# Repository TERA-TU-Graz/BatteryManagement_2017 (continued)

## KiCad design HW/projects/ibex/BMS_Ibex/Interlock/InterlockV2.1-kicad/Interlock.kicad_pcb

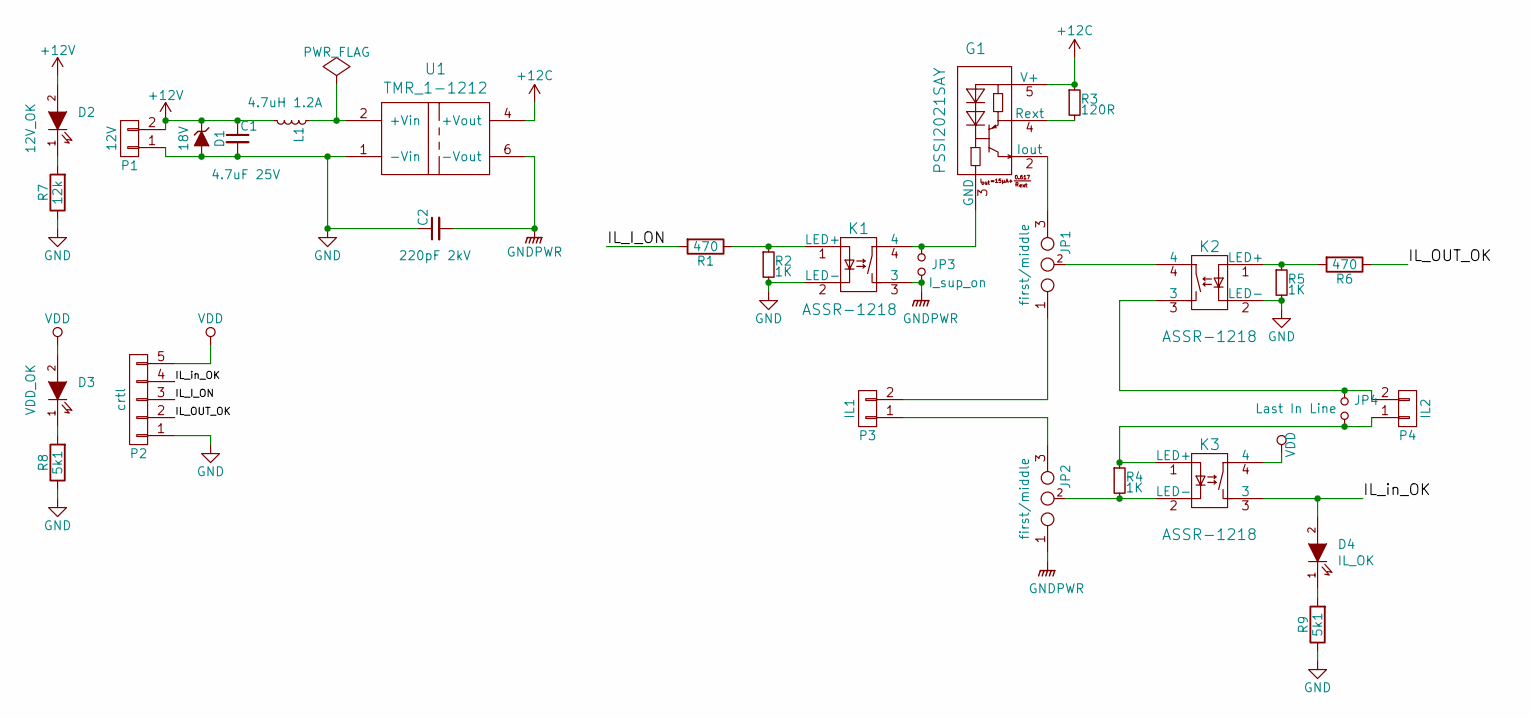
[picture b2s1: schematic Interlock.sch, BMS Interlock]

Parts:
C1: 4.7uF 25V; C_0805in
C2: 220pF 2kV; C_1206in_HV
D1: 18V; DO-214AA
D2: 12V_OK; LED_0805
D3: VDD_OK; LED_0805
D4: IL_OK; LED_0805
G1: PSSI2021SAY
JP1, JP2: first/middle; SOLDERJUMPER_3
JP3: I_sup_on; SOLDERJUMPER_2
JP4: Last In Line; SOLDERJUMPER_2
K1, K2, K3: ASSR-1218; SO-4
L1: 4.7uH 1.2A; L_muarta_LQH32PN
P1: 12V; JST_XH_B02B-XH-A_02x2.50mm_Straight
P2: crtl; JST_XH_B05B-XH-A_05x2.50mm_Straight
P3: IL1; JST_EH_B02B-EH-A_02x2.50mm_Straight
P4: IL2; JST_EH_B02B-EH-A_02x2.50mm_Straight
R1, R6: 470; R_0603in
R2, R4, R5: 1K; R_0603in
R3: 120R; R_0603in
R7: 12k; R_0603in
R8, R9: 5k1; R_0603in
U1: TMR_1-1212; TMR_1-XX1X

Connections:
+12C: G1.5 (V+), R3.1, U1.4 (+Vout)
+12V: C1.1, D1.1 (K), D2.2 (A), L1.2, P1.2
/IL_I_ON: P2.3, R1.2
/IL_OUT_OK: P2.2, R6.1
/IL_in_OK: D4.2 (A), K3.3, P2.4
GND: C1.2, C2.1, D1.2 (A), K1.2 (LED-), K2.2 (LED-), P1.1, P2.1, R2.2, R5.2, R7.1, R8.1, R9.1, U1.1 (-Vin)
GNDPWR: C2.2, JP2.1 (m), JP3.2, K1.3, U1.6 (-Vout)
unnamed: D2.1 (K), R7.2
unnamed: D3.1 (K), R8.2
unnamed: D4.1 (K), R9.2
unnamed: G1.2 (Iout), JP1.3
unnamed: G1.3 (GND), JP3.1, K1.4
unnamed: G1.4 (Rext), R3.2
unnamed: JP1.1 (m), P3.2
unnamed: JP1.2, K2.4
unnamed: JP2.2, K3.2 (LED-), R4.2
unnamed: JP2.3, P3.1
unnamed: JP4.1, K2.3, P4.2
unnamed: JP4.2, K3.1 (LED+), P4.1, R4.1
unnamed: K1.1 (LED+), R1.1, R2.1
unnamed: K2.1 (LED+), R5.1, R6.2
unnamed: L1.1, U1.2 (+Vin)
VDD: D3.2 (A), K3.4, P2.5

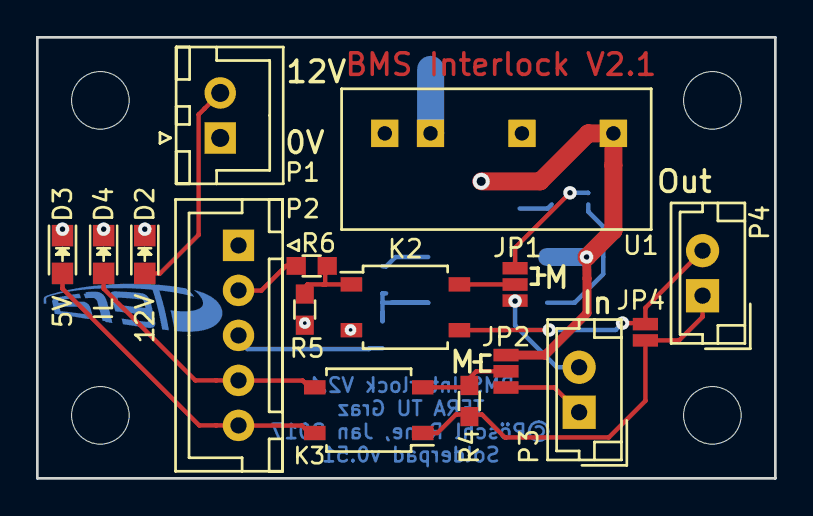
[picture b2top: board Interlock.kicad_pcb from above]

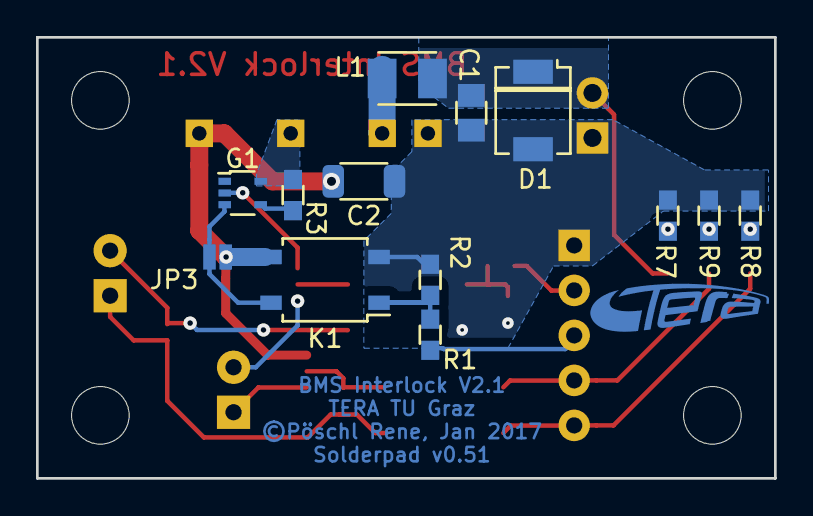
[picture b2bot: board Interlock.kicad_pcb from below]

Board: 2 copper layers, 41.0 x 24.5 mm, 30 parts (14 on the bottom side), 23 nets.

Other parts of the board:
svg2mod: G***; TERA_TextOnly_Cu_2.5x9.5mm

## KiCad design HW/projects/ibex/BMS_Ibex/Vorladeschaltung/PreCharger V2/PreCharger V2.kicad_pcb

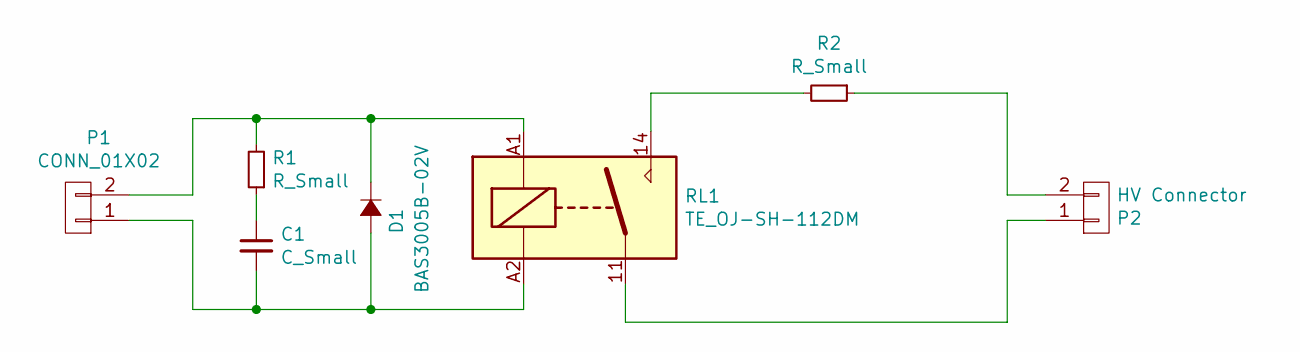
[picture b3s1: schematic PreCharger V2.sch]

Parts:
C1: C_Small; C_0805in
D1: BAS3005B-02V; BAS3005B-02V__sc79
P1: CONN_01X02; JST_XH_B02B-XH-A_02x2.50mm_Straight
P2: HV Connector; MCV_1.5_2-GF-3.5_MountHole
R1: R_Small; R_0805in
R2: R_Small; R_WH25
RL1: TE_OJ-SH-112DM; RELAIS-TE-OJ

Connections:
unnamed: C1.1, R1.1
unnamed: C1.2, D1.2 (A), P1.1, RL1.A2
unnamed: D1.1 (K), P1.2, R1.2, RL1.A1
unnamed: P2.1, RL1.11
unnamed: P2.2, R2.1
unnamed: R2.2, RL1.14

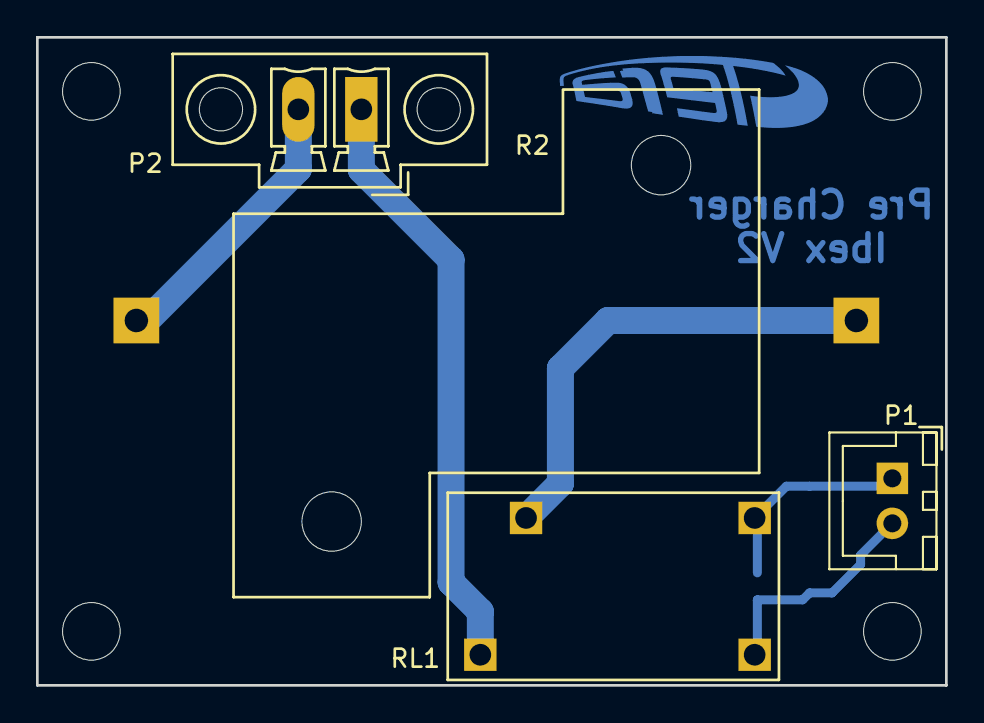
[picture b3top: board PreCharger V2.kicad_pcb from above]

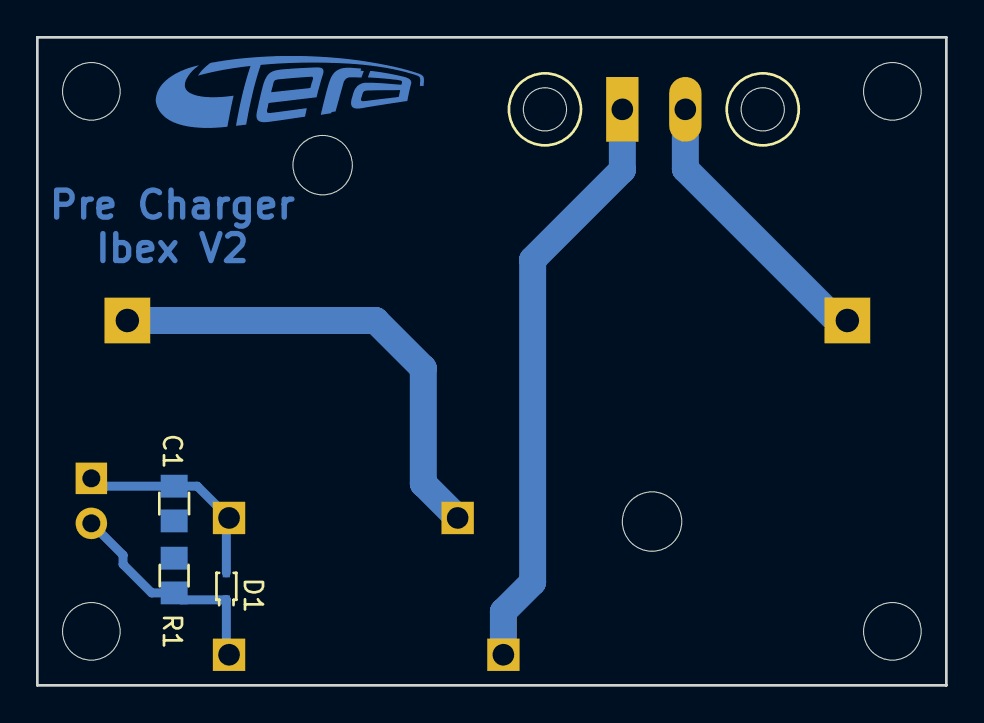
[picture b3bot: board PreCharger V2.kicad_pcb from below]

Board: 2 copper layers, 50.5 x 36.0 mm, 8 parts (4 on the bottom side), 6 nets.

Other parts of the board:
svg2mod: G***; TERA_TextOnly_Cu_3.75x14mm

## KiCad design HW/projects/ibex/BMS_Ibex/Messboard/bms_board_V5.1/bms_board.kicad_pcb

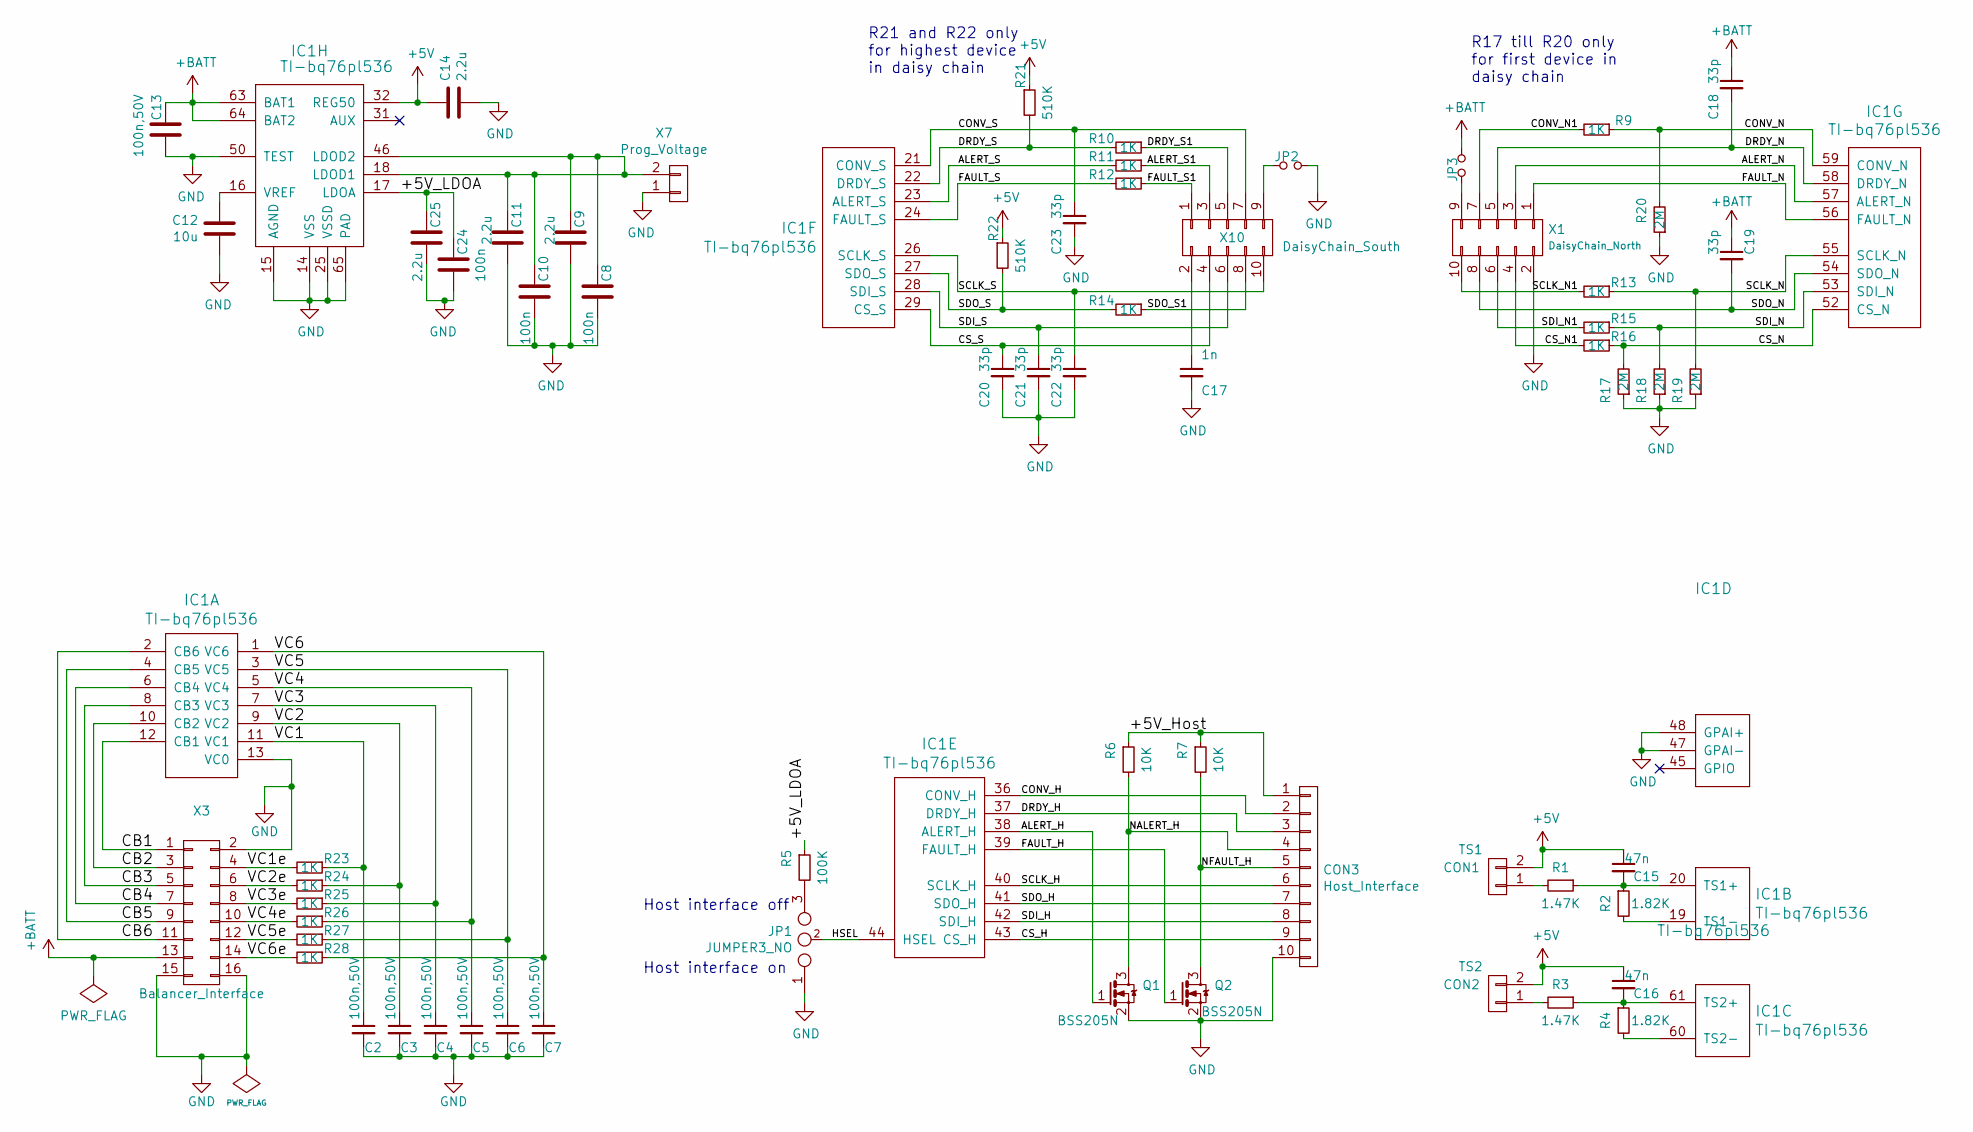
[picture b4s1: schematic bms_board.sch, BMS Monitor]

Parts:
C2, C3, C4, C5, C6, C7, C13: 100n,50V; C_0805in
C8, C10, C24: 100n; C_0603in
C9, C11, C14, C25: 2.2u; C_0805in
C12: 10u; C_0805in
C15, C16: 47n; C_0603in
C17: 1n; C_0603in
C18, C19, C20, C21, C22, C23: 33p; C_0603in
CON1: TS1; Molex_PicoBlade_53398-0271_02x1.25mm_Straight
CON2: TS2; Molex_PicoBlade_53398-0271_02x1.25mm_Straight
CON3: Host_Interface; Molex_PicoBlade_53261-1071_10x1.25mm_Angled
IC1: TI-bq76pl536; TI_bq76PL536
JP1: JUMPER3_NO; SOLDERJUMPER_3
JP2, JP3: Jumper_NO_Small; SOLDERJUMPER_2_1mm
Q1, Q2: BSS205N
R1, R3: 1.47K; R_0603in
R2, R4: 1.82K; R_0603in
R5: 100K; R_0603in
R6, R7: 10K; R_0603in
R9, R10, R11, R12, R13, R14, R15, R16, R23, R24, R25, R26, R27, R28: 1K; R_0603in
R17, R18, R19, R20: 2M; R_0603in
R21, R22: 510K; R_0603in
X1: DaisyChain_North; IDC_02X05_Angled
X3: Balancer_Interface; Socket_Strip_Straight_2x08
X7: Prog_Voltage; Socket_Strip_Straight_1x02
X10: DaisyChain_South; IDC_02X05_Angled

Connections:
+5V: C14.1, C15.1, C16.1, CON1.2, CON2.2, IC1.32 (REG50), R21.1, R22.1
+BATT: C13.2, C18.1, C19.1, IC1.63 (BAT1), IC1.64 (BAT2), JP3.1, X3.13
/+5V_Host: CON3.1, R6.1, R7.1
/+5V_LDOA: C24.1, C25.1, IC1.17 (LDOA), R5.1
/ALERT_H: IC1.38 (ALERT_H), Q1.1 (G)
/ALERT_N: IC1.57 (ALERT_N), X1.3
/ALERT_S: IC1.23 (ALERT_S), R11.2
/ALERT_S1: R11.1, X10.3
/CB1: IC1.12 (CB1), X3.1
/CB2: IC1.10 (CB2), X3.3
/CB3: IC1.8 (CB3), X3.5
/CB4: IC1.6 (CB4), X3.7
/CB5: IC1.4 (CB5), X3.9
/CB6: IC1.2 (CB6), X3.11
/CONV_H: CON3.2, IC1.36 (CONV_H)
/CONV_N: IC1.59 (CONV_N), R9.1, R20.2
/CONV_N1: R9.2, X1.7
/CONV_S: C23.1, IC1.21 (CONV_S), X10.7
/CS_H: CON3.9, IC1.43 (CS_H)
/CS_N: IC1.52 (CS_N), R16.1, R17.2
/CS_N1: R16.2, X1.4
/CS_S: C20.1, IC1.29 (CS_S), X10.4
/DRDY_H: CON3.3, IC1.37 (DRDY_H)
/DRDY_N: C18.2, IC1.58 (DRDY_N), X1.5
/DRDY_S: IC1.22 (DRDY_S), R10.2, R21.2
/DRDY_S1: R10.1, X10.5
/FAULT_H: IC1.39 (FAULT_H), Q2.1 (G)
/FAULT_N: IC1.56 (FAULT_N), X1.1
/FAULT_S: IC1.24 (FAULT_S), R12.2
/FAULT_S1: R12.1, X10.1
/HSEL: IC1.44 (HSEL), JP1.2
/NALERT_H: CON3.4, Q1.3 (D), R6.2
/NFAULT_H: CON3.5, Q2.3 (D), R7.2
/SCLK_H: CON3.6, IC1.40 (SCLK_H)
/SCLK_N: IC1.55 (SCLK_N), R13.1, R19.2
/SCLK_N1: R13.2, X1.10
/SCLK_S: C22.1, IC1.26 (SCLK_S), X10.10
/SDI_H: CON3.8, IC1.42 (SDI_H)
/SDI_N: IC1.53 (SDI_N), R15.1, R18.2
/SDI_N1: R15.2, X1.6
/SDI_S: C21.1, IC1.28 (SDI_S), X10.6
/SDO_H: CON3.7, IC1.41 (SDO_H)
/SDO_N: C19.2, IC1.54 (SDO_N), X1.8
/SDO_S: IC1.27 (SDO_S), R14.2, R22.2
/SDO_S1: R14.1, X10.8
/VC1: C2.1, IC1.11 (VC1), R23.1
/VC1e: R23.2, X3.4
/VC2: C3.1, IC1.9 (VC2), R24.1
/VC2e: R24.2, X3.6
/VC3: C4.1, IC1.7 (VC3), R25.1
/VC3e: R25.2, X3.8
/VC4: C5.1, IC1.5 (VC4), R26.1
/VC4e: R26.2, X3.10
/VC5: C6.1, IC1.3 (VC5), R27.1
/VC5e: R27.2, X3.12
/VC6: C7.1, IC1.1 (VC6), R28.1
/VC6e: R28.2, X3.14
GND: C2.2, C3.2, C4.2, C5.2, C6.2, C7.2, C8.2, C9.2, C10.2, C11.2, C12.2, C13.1, C14.2, C17.2, C20.2, C21.2, C22.2, C23.2, C24.2, C25.2, CON3.10, IC1.13 (VC0), IC1.14 (VSS), IC1.15 (AGND), IC1.25 (VSSD), IC1.33 (VSS), IC1.34 (VSS), IC1.35 (VSS), IC1.47 (GPAI-), IC1.48 (GPAI+), IC1.49 (VSSD), IC1.50 (TEST), IC1.65 (PAD), JP1.1 (m), JP2.1, Q1.2 (S), Q2.2 (S), R17.1, R18.1, R19.1, R20.1, X1.2, X3.2, X3.15, X3.16, X7.1
unnamed: C8.1, C9.1, C10.1, C11.1, IC1.18 (LDOD1), IC1.46 (LDOD2), X7.2
unnamed: C12.1, IC1.16 (VREF)
unnamed: C15.2, IC1.20 (TS1+), R1.1, R2.1
unnamed: C16.2, IC1.61 (TS2+), R3.1, R4.1
unnamed: C17.1, X10.2
unnamed: CON1.1, R1.2
unnamed: CON2.1, R3.2
unnamed: IC1.19 (TS1-), R2.2
unnamed: IC1.60 (TS2-), R4.2
unnamed: JP1.3, R5.2
unnamed: JP2.2, X10.9
unnamed: JP3.2, X1.9

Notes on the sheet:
R21 and R22 only for highest device in daisy chain
R17 till R20 only for first device in daisy chain
Host interface on
Host interface off

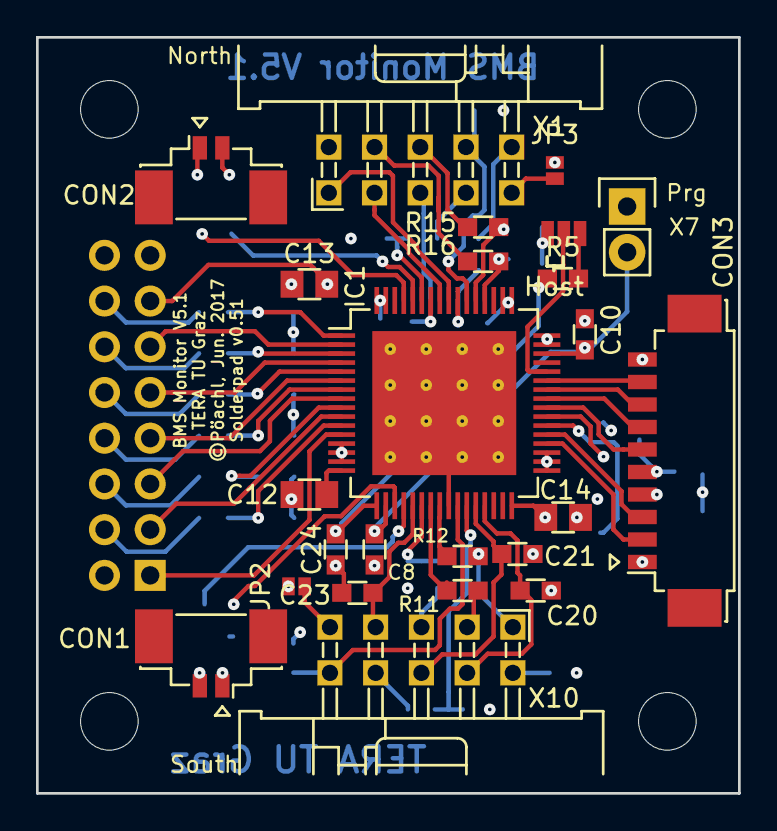
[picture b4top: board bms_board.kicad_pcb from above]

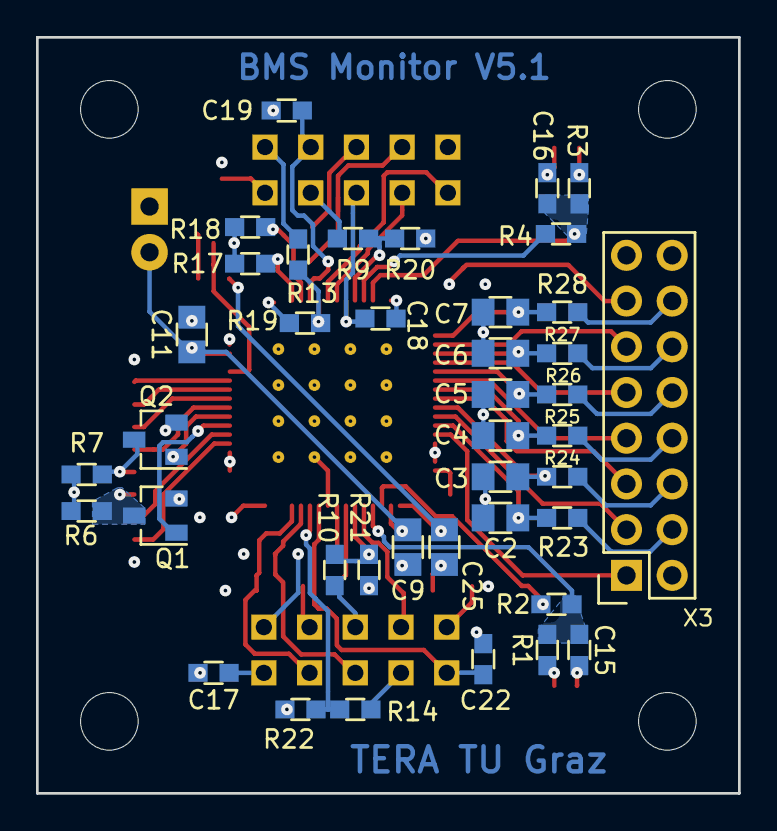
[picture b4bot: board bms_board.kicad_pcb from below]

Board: 4 copper layers, 39.0 x 42.0 mm, 64 parts (40 on the bottom side), 70 nets.

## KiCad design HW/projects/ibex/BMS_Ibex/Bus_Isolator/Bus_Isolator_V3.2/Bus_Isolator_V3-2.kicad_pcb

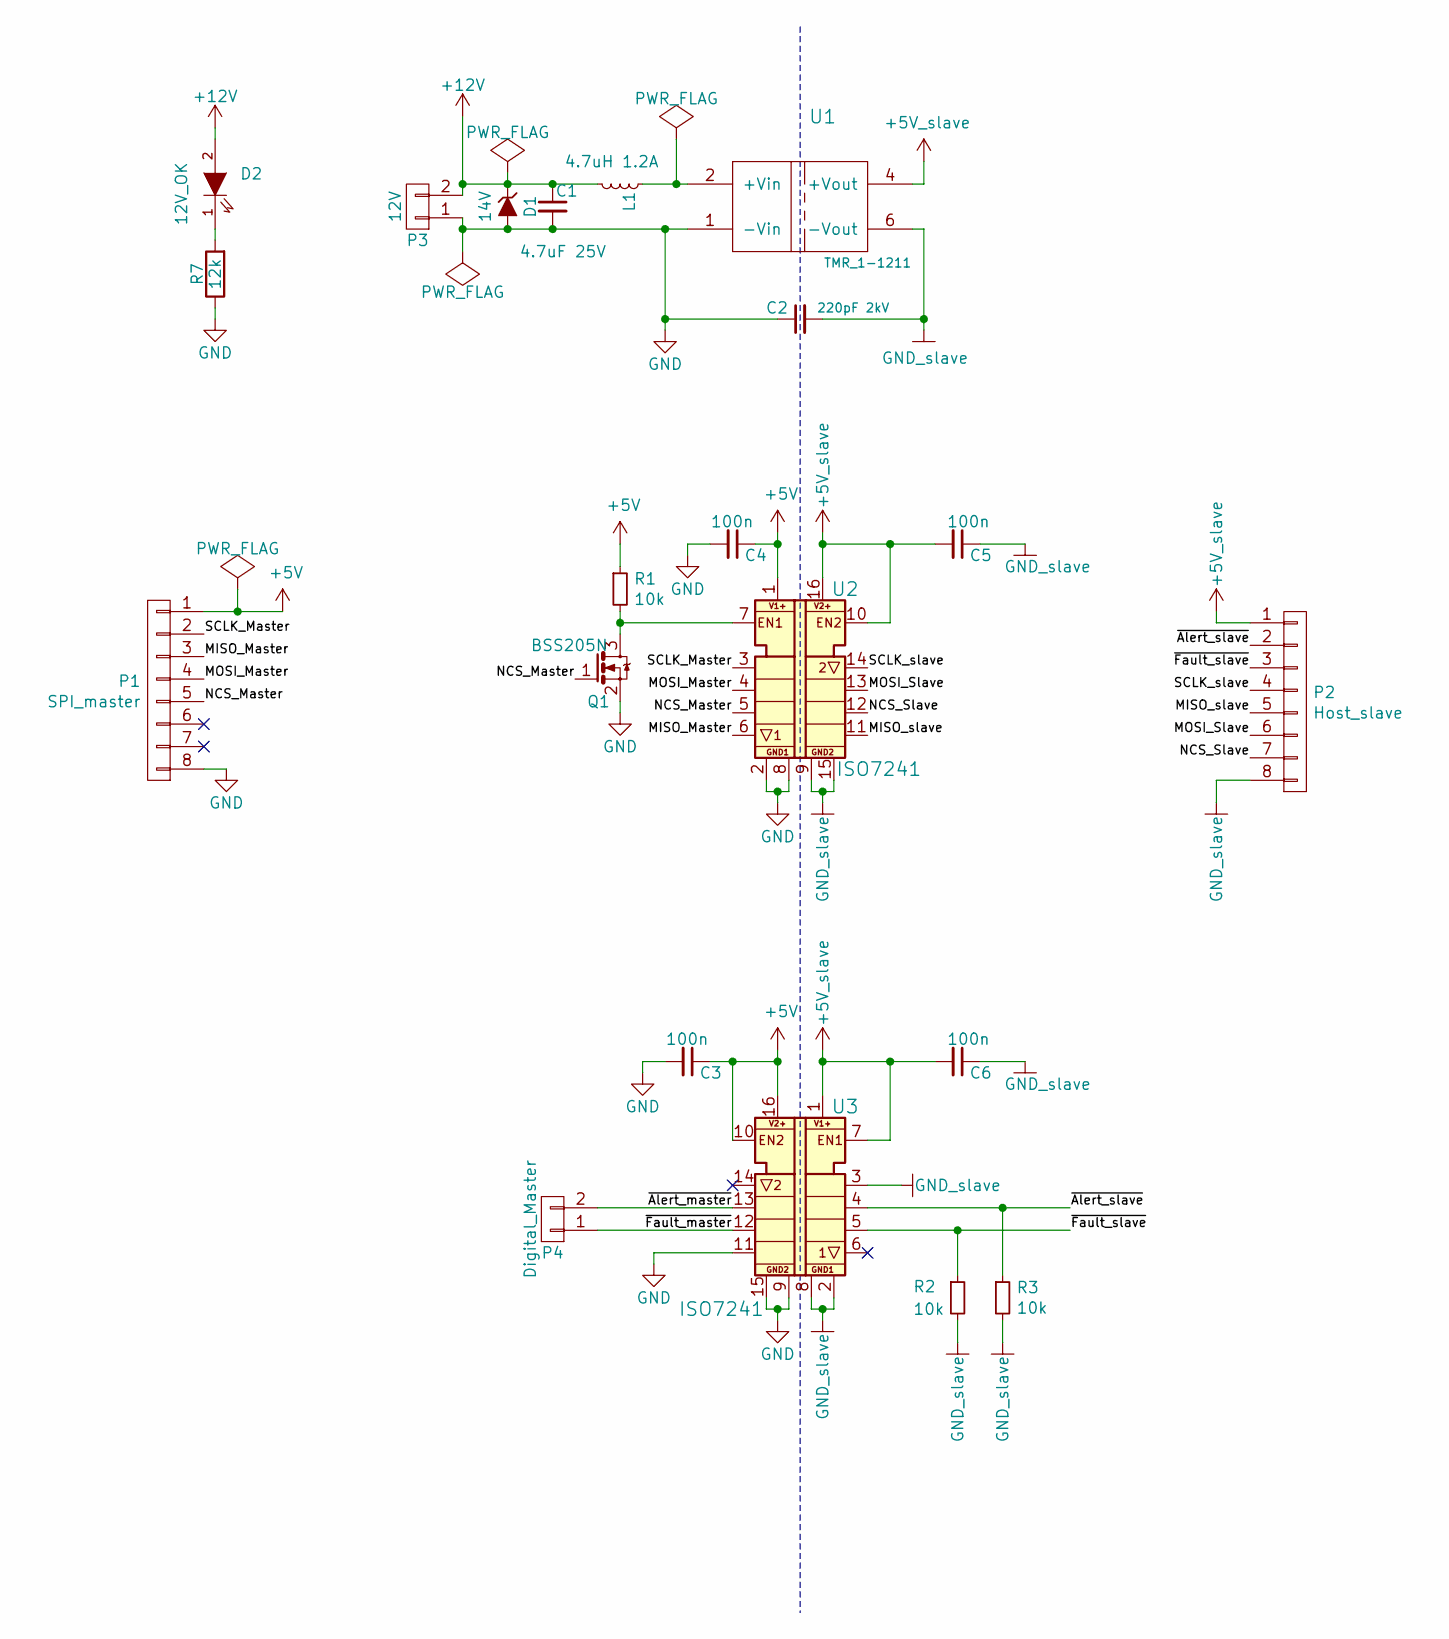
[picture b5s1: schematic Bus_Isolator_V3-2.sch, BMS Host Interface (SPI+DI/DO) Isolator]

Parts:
C1: 4.7uF 25V; C_0805in
C2: 220pF 2kV; C_1206in_HV
C3, C4, C5, C6: 100n; C_0805in
D1: 14V; SOD128
D2: 12V_OK; LED_0805
L1: 4.7uH 1.2A; L_muarta_LQH32PN
P1: SPI_master; Molex_PicoBlade_53398-0871_08x1.25mm_Straight
P2: Host_slave; Molex_PicoBlade_53398-0871_08x1.25mm_Straight
P3: 12V; JST_XH_B02B-XH-A_02x2.50mm_Straight
P4: Digital_Master; JST_EH_B02B-EH-A_02x2.50mm_Straight
Q1: BSS205N
R1, R2, R3: 10k; R_0805in
R7: 12k; R_0603in
U1: TMR_1-1211; TMR_1-XX1X
U2, U3: ISO7241

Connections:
+5V: C3.1, C4.1, P1.1, R1.1, U2.1 (V1+), U3.10 (EN2), U3.16 (V2+)
+5V_slave: C5.2, C6.2, P2.1, U1.4 (+Vout), U2.10 (EN2), U2.16 (V2+), U3.1 (V1+), U3.7 (EN1)
+12V: C1.1, D1.1 (K), D2.2 (A), L1.2, P3.2
/MISO_Master: P1.3, U2.6 (OUT1)
/MISO_slave: P2.5, U2.11 (IN1)
/MOSI_Master: P1.4, U2.4 (IN3)
/MOSI_Slave: P2.6, U2.13 (OUT3)
/NCS_Master: P1.5, Q1.1 (G), U2.5 (IN4)
/NCS_Slave: P2.7, U2.12 (OUT4)
/SCLK_Master: P1.2, U2.3 (IN2)
/SCLK_slave: P2.4, U2.14 (OUT2)
/~Alert_master: P4.2, U3.13 (OUT3)
/~Alert_slave: P2.2, R3.1, U3.4 (IN3)
/~Fault_master: P4.1, U3.12 (OUT4)
/~Fault_slave: P2.3, R2.1, U3.5 (IN4)
GND: C1.2, C2.1, C3.2, C4.2, D1.2 (A), P1.8, P3.1, Q1.2 (S), R7.1, U1.1 (-Vin), U2.2 (GND1), U2.8 (GND1), U3.9 (GND2), U3.11 (IN1), U3.15 (GND2)
GND_slave: C2.2, C5.1, C6.1, P2.8, R2.2, R3.2, U1.6 (-Vout), U2.9 (GND2), U2.15 (GND2), U3.2 (GND1), U3.3 (IN2), U3.8 (GND1)
unnamed: D2.1 (K), R7.2
unnamed: L1.1, U1.2 (+Vin)
unnamed: Q1.3 (D), R1.2, U2.7 (EN1)

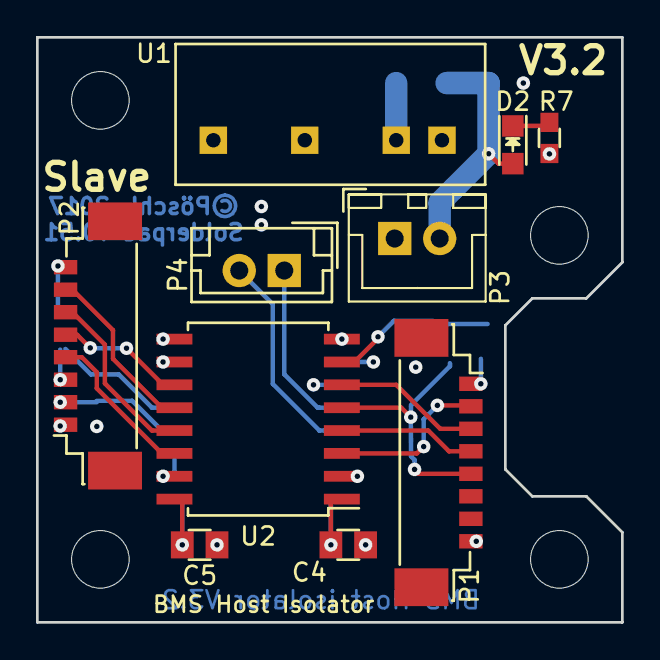
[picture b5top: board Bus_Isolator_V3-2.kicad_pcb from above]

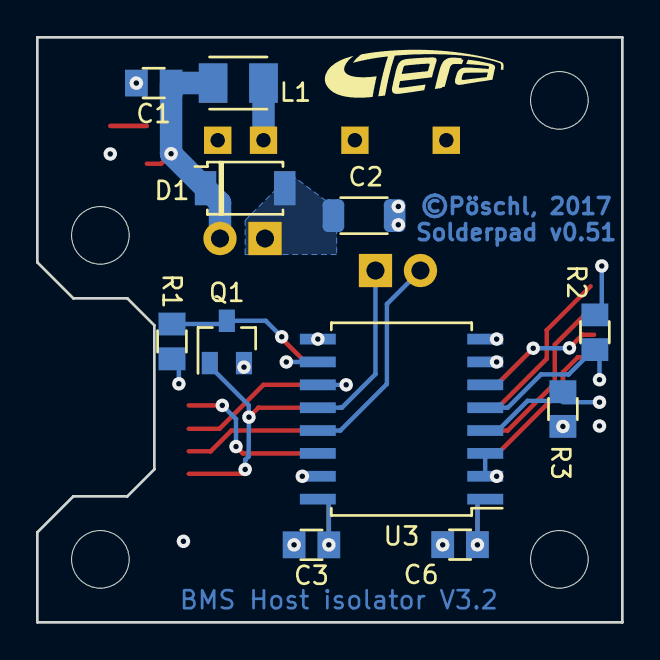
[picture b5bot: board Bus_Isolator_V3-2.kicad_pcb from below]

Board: 4 copper layers, 32.5 x 32.5 mm, 22 parts (12 on the bottom side), 20 nets.

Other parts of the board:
svg2mod: G***; TERA_TextOnly_SilkS_2.5x9.5mm

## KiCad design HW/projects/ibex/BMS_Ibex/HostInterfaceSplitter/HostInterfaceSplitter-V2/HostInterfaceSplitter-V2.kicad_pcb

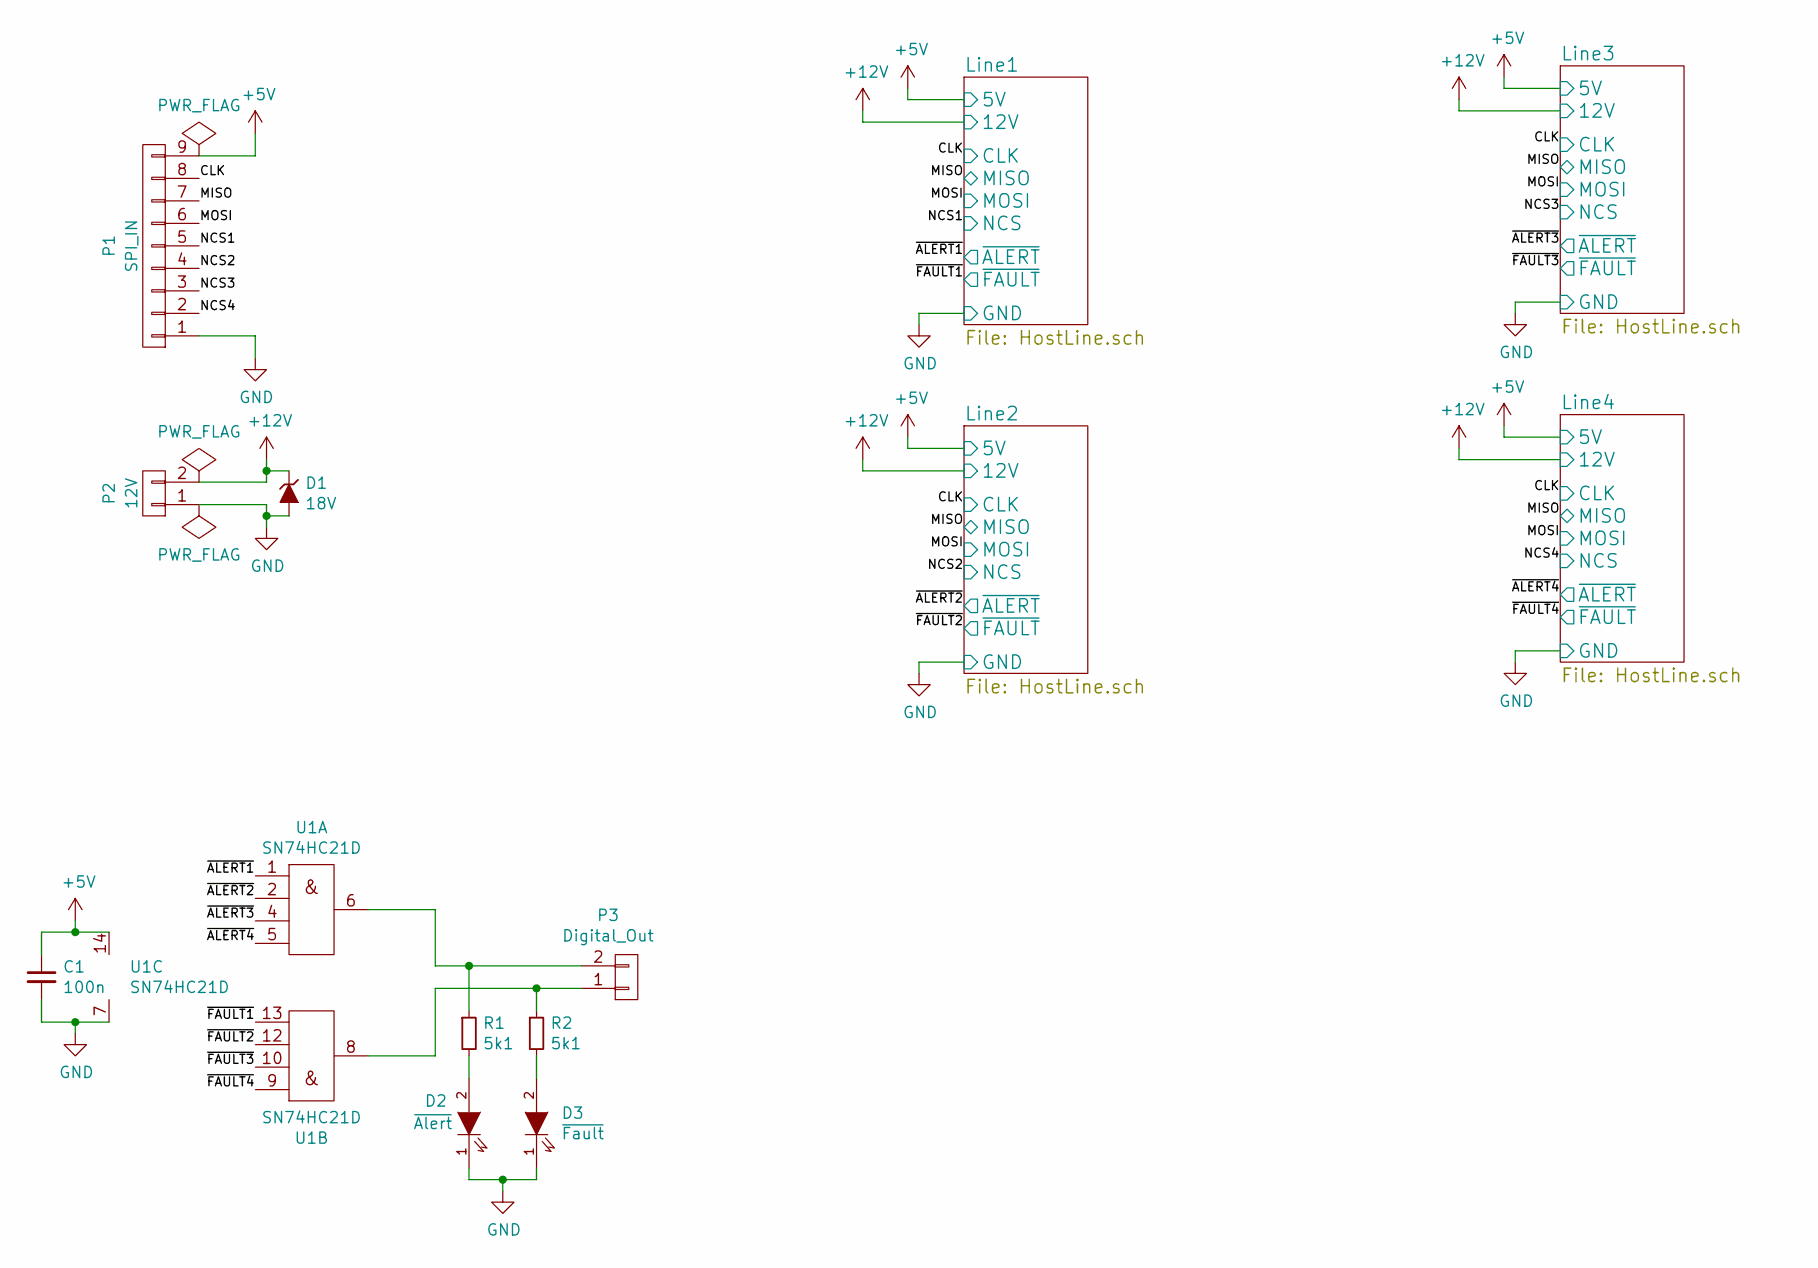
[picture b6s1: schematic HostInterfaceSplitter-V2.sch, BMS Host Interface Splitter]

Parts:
C1: 100n; C_0805in
D1: 18V; DO-214AA_with_vias_in_pad
D2: ~Alert; LED_0805
D3: ~Fault; LED_0805
P1: SPI_IN; JST_XH_B09B-XH-A_09x2.50mm_Straight
P2: 12V; JST_XH_B02B-XH-A_02x2.50mm_Straight
P3: Digital_Out; JST_EH_B02B-EH-A_02x2.50mm_Straight
R1, R2: 5k1; C_0805in
U1: SN74HC21D

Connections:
+5V: C1.1, P1.9, U1.14 (VCC); also elsewhere on the board
+12V: D1.1 (K), P2.2; also elsewhere on the board
/CLK: P1.8; also elsewhere on the board
/MISO: P1.7; also elsewhere on the board
/MOSI: P1.6; also elsewhere on the board
/NCS1: P1.5; also elsewhere on the board
/NCS2: P1.4; also elsewhere on the board
/NCS3: P1.3; also elsewhere on the board
/NCS4: P1.2; also elsewhere on the board
/~ALERT1: U1.1 (1A); also elsewhere on the board
/~ALERT2: U1.2 (1B); also elsewhere on the board
/~ALERT3: U1.4 (1C); also elsewhere on the board
/~ALERT4: U1.5 (1D); also elsewhere on the board
/~FAULT1: U1.13 (2D); also elsewhere on the board
/~FAULT2: U1.12 (2C); also elsewhere on the board
/~FAULT3: U1.10 (2B); also elsewhere on the board
/~FAULT4: U1.9 (2A); also elsewhere on the board
GND: C1.2, D1.2 (A), D2.1 (K), D3.1 (K), P1.1, P2.1, U1.7 (GND); also elsewhere on the board
unnamed: D2.2 (A), R1.2
unnamed: D3.2 (A), R2.2
unnamed: P3.1, R2.1, U1.8 (2Y)
unnamed: P3.2, R1.1, U1.6 (1Y)

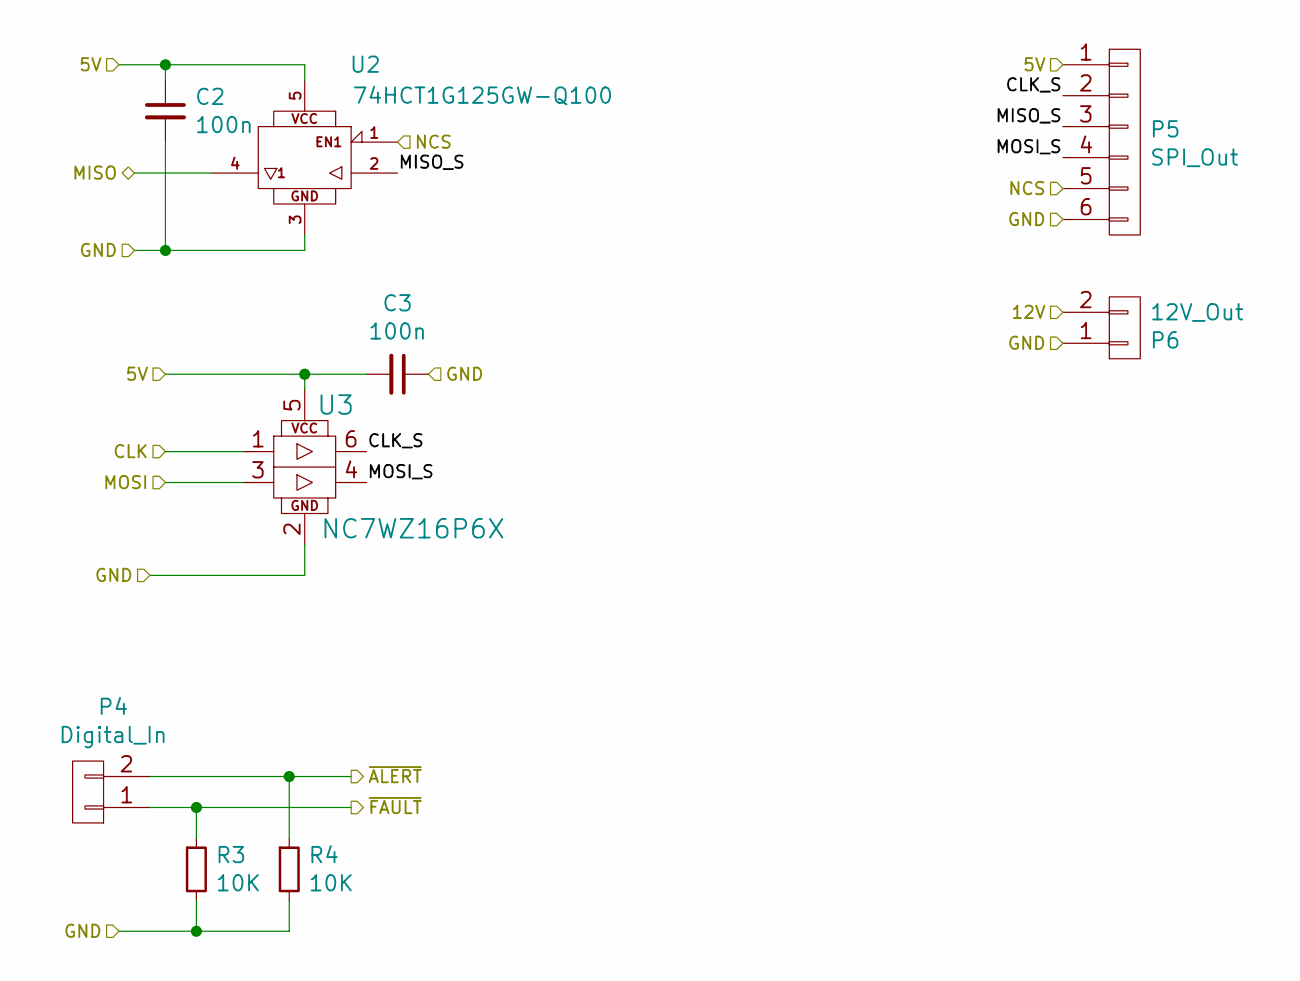
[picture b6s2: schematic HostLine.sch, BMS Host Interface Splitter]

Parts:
C2, C3: 100n; C_0603in
P4: Digital_In; JST_EH_B02B-EH-A_02x2.50mm_Straight
P5: SPI_Out; Molex_PicoBlade_53398-0671_06x1.25mm_Straight
P6: 12V_Out; JST_XH_B02B-XH-A_02x2.50mm_Straight
R3, R4: 10K; R_0805in
U2: 74HCT1G125GW-Q100; 74HCT1G125GW-Q100H
U3: NC7WZ16P6X

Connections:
+5V: C2.1, C3.2, P5.1, U2.5 (VCC), U3.5 (VCC); also elsewhere on the board
+12V: P6.2; also elsewhere on the board
/CLK: U3.1 (A1); also elsewhere on the board
/Line1/CLK_S: P5.2, U3.6 (Y1)
/Line1/MISO_S: P5.3, U2.2 (A)
/Line1/MOSI_S: P5.4, U3.4 (Y2)
/MISO: U2.4 (O); also elsewhere on the board
/MOSI: U3.3 (A2); also elsewhere on the board
/NCS1: P5.5, U2.1 (EN); also elsewhere on the board
/~ALERT1: P4.2, R4.1; also elsewhere on the board
/~FAULT1: P4.1, R3.1; also elsewhere on the board
GND: C2.2, C3.1, P5.6, P6.1, R3.2, R4.2, U2.3 (GND), U3.2 (GND); also elsewhere on the board

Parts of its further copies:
C4, C5, C6, C7, C8, C9: 100n; C_0603in
P7, P10, P13: Digital_In; JST_EH_B02B-EH-A_02x2.50mm_Straight
P8, P11, P14: SPI_Out; Molex_PicoBlade_53398-0671_06x1.25mm_Straight
P9, P12, P15: 12V_Out; JST_XH_B02B-XH-A_02x2.50mm_Straight
R5, R6, R7, R8, R9, R10: 10K; R_0805in
U4, U6, U8: 74HCT1G125GW-Q100; 74HCT1G125GW-Q100H
U5, U7, U9: NC7WZ16P6X

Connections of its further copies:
+5V: C4.1, C5.2, C6.1, C7.2, C8.1, C9.2, P8.1, P11.1, P14.1, U4.5 (VCC), U5.5 (VCC), U6.5 (VCC), U7.5 (VCC), U8.5 (VCC), U9.5 (VCC); also elsewhere on the board
+12V: P9.2, P12.2, P15.2; also elsewhere on the board
/CLK: U5.1 (A1), U7.1 (A1), U9.1 (A1); also elsewhere on the board
/Line2/CLK_S: P8.2, U5.6 (Y1)
/Line2/MISO_S: P8.3, U4.2 (A)
/Line2/MOSI_S: P8.4, U5.4 (Y2)
/Line3/CLK_S: P11.2, U7.6 (Y1)
/Line3/MISO_S: P11.3, U6.2 (A)
/Line3/MOSI_S: P11.4, U7.4 (Y2)
/Line4/CLK_S: P14.2, U9.6 (Y1)
/Line4/MISO_S: P14.3, U8.2 (A)
/Line4/MOSI_S: P14.4, U9.4 (Y2)
/MISO: U4.4 (O), U6.4 (O), U8.4 (O); also elsewhere on the board
/MOSI: U5.3 (A2), U7.3 (A2), U9.3 (A2); also elsewhere on the board
/NCS2: P8.5, U4.1 (EN); also elsewhere on the board
/NCS3: P11.5, U6.1 (EN); also elsewhere on the board
/NCS4: P14.5, U8.1 (EN); also elsewhere on the board
/~ALERT2: P7.2, R6.1; also elsewhere on the board
/~ALERT3: P10.2, R8.1; also elsewhere on the board
/~ALERT4: P13.2, R10.1; also elsewhere on the board
/~FAULT2: P7.1, R5.1; also elsewhere on the board
/~FAULT3: P10.1, R7.1; also elsewhere on the board
/~FAULT4: P13.1, R9.1; also elsewhere on the board
GND: C4.2, C5.1, C6.2, C7.1, C8.2, C9.1, P8.6, P9.1, P11.6, P12.1, P14.6, P15.1, R5.2, R6.2, R7.2, R8.2, R9.2, R10.2, U4.3 (GND), U5.2 (GND), U6.3 (GND), U7.2 (GND), U8.3 (GND), U9.2 (GND); also elsewhere on the board

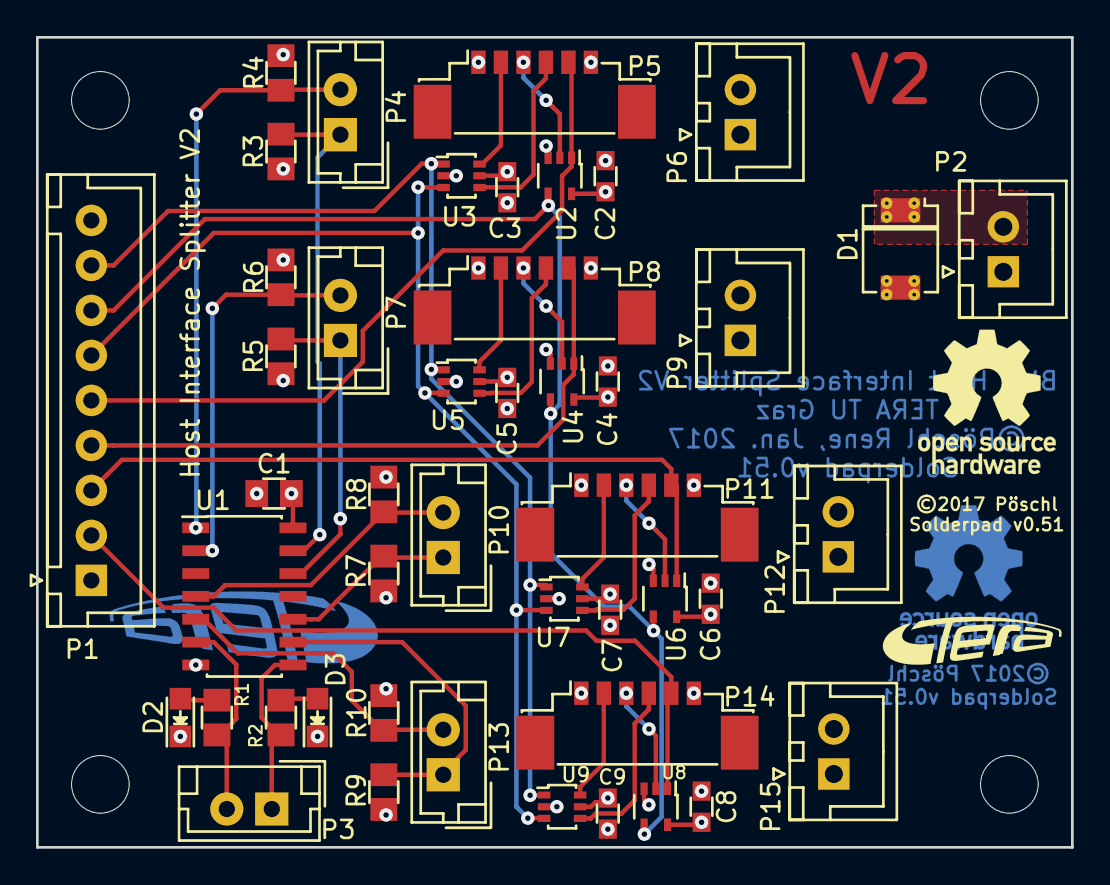
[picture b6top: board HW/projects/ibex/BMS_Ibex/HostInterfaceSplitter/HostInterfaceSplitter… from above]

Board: 4 copper layers, 57.5 x 45.0 mm, 48 parts (1 on the bottom side), 34 nets.

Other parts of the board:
svg2mod: G***; TERA_TextOnly_SilkS_2.5x9.5mm
svg2mod#2: G***; TERA_TextOnly_Cu_3.75x14mm
